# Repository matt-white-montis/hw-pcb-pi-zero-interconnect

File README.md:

# hw-pcb-pi-zero-interconnect
Franke specific PCB interconnect board for a Pi Zero that standardizes the GPIO breakout to a common Molex Micro-Fit connector.

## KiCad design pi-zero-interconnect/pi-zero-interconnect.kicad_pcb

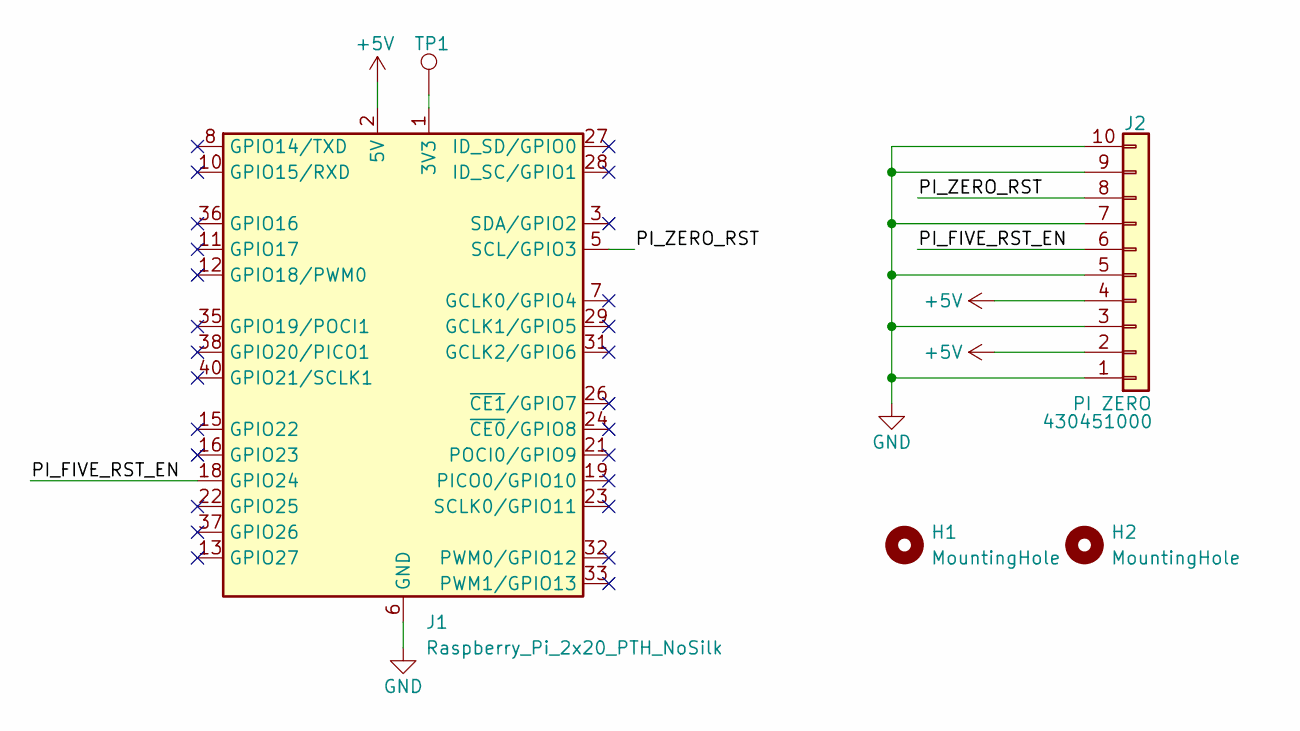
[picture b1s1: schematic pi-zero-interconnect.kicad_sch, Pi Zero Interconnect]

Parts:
H1, H2: MountingHole; MountingHole_2.7mm_M2.5_DIN965_Pad_TopBottom
J1: Raspberry_Pi_2x20_PTH_NoSilk; PinHeader_2x20_P2.54mm_Vertical
J2: PI ZERO; Molex_Micro-Fit_3.0_43045-1000_2x05_P3.00mm_Horizontal; Part Number 430451000
TP1: 3V3; TestPoint_Pad_D1.0mm

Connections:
+5V: J1.2 (5V), J1.4 (5V), J2.2, J2.4
/PI_FIVE_RST_EN: J1.18 (GPIO24), J2.6
/PI_ZERO_RST: J1.5 (SCL/GPIO3), J2.8
GND: J1.6 (GND), J1.9 (GND), J1.14 (GND), J1.20 (GND), J1.25 (GND), J1.30 (GND), J1.34 (GND), J1.39 (GND), J2.1, J2.3, J2.5, J2.7, J2.9, J2.10
unnamed: J1.1 (3V3), J1.17 (3V3), TP1.1 (1_1)

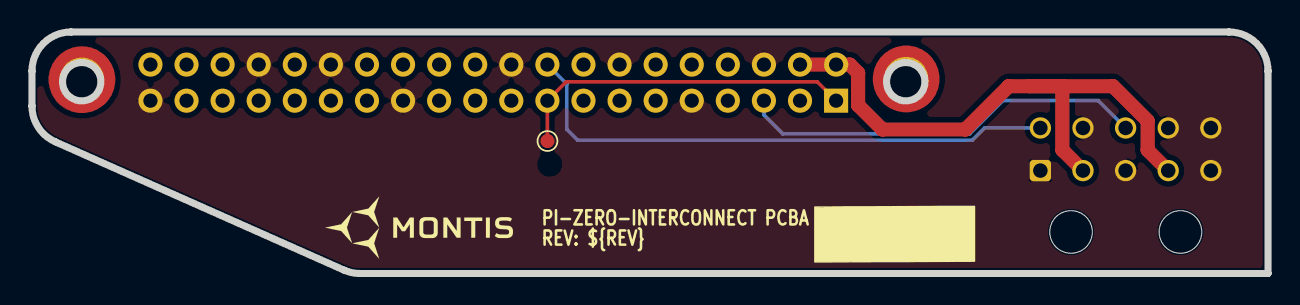
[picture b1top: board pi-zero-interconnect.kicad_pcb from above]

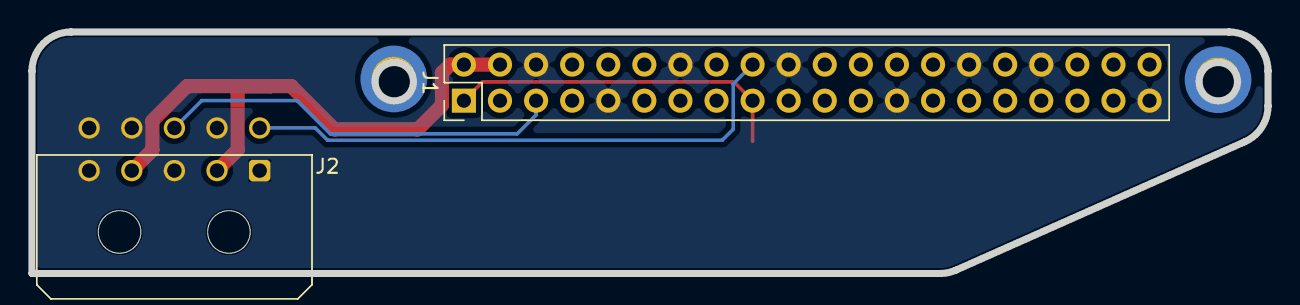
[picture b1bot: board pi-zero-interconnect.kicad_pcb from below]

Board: 2 copper layers, 87.0 x 17.0 mm, 5 parts (2 on the bottom side), 5 nets.

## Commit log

2026-04-23 initial layout
2026-04-24 REV 0.1.0 intial Release
